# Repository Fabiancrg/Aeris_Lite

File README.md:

| Supported Targets | ESP32-C6 | ESP32-H2 |
| ----------------- |  -------- | -------- |

# Zigbee Air Quality Sensor - Aeris

This project implements a Zigbee Router that reads air quality sensors and exposes them as standard Zigbee sensor endpoints with **real-time RGB LED visual indicators**.

## Key Features

✅ **7 Zigbee Endpoints**: Temperature, Humidity, Pressure, VOC Index, NOx Index, CO2, LED Config, Status LED  
✅ **4 High-Precision Sensors**: SHT45, LPS22HB, SGP41, SCD40  
✅ **4 RGB Status LEDs**: Independent visual feedback for CO2, VOC, NOx, and Humidity  
✅ **Configurable Thresholds**: Adjust warning/danger levels via Zigbee2MQTT  
✅ **Zigbee Router**: Can accept other devices (max 10 children)  
✅ **OTA Support**: Firmware updates over Zigbee  
✅ **Factory Reset**: Boot button for easy network reset

## Hardware Requirements

- ESP32-C6 development board (or compatible)
- Air quality sensors:
  - **SHT45 Temperature and Humidity sensor** via I2C
  - **LPS22HB Pressure sensor** via I2C
  - **SGP41 VOC and NOx sensor** via I2C
  - **SCD40 CO2 sensor** via I2C
- **5× SK6812/WS2812B RGB LEDs** in daisy-chain configuration (air quality visual indicators)
  - Single GPIO20 with SN74AHCT1G125 buffer for all LEDs
  - LED chain: CO2 → VOC → NOx → Humidity → Status
- I2C connection (SDA/SCL pins configurable)
- **Power supply**: 5V USB, 500mA minimum recommended

## Features

The Zigbee air quality sensor exposes the following sensor endpoints:

### Endpoint 1: Temperature and Humidity Sensor
- **Temperature Measurement Cluster (0x0402)**: Temperature in °C
- **Relative Humidity Measurement Cluster (0x0405)**: Humidity in %
- **Sensor**: Sensirion SHT45 (I2C)
- **Temperature Range**: -40°C to +125°C
- **Temperature Accuracy**: ±0.1°C (typical, 15-40°C)
- **Humidity Range**: 0-100% RH
- **Humidity Accuracy**: ±1.0% RH (typical, 25-75% RH)
- **Measurement Time**: 8.2ms (high precision mode)
- **Conversion**: Temperature: T = -45 + 175×(S/65535), Humidity: RH = -6 + 125×(S/65535)
- **Calibration Offsets**: Custom attributes (0xF010, 0xF011) for temperature/humidity adjustment
- **Sensor Refresh Interval**: Configurable update rate (10-3600s, default 30s) via attribute 0xF012

### Endpoint 2: Pressure Sensor
- **Pressure Measurement Cluster (0x0403)**: Atmospheric pressure in hPa
- **Sensor**: STMicroelectronics LPS22HB (I2C)
- **Update Rate**: On-demand (one-shot mode for power savings)
- **Range**: 260-1260 hPa
- **Accuracy**: ±0.025 hPa (typical)
- **Measurement Time**: ~15ms per reading

### Endpoint 3: VOC Index Sensor
- **Analog Input Cluster (0x000C)**: VOC Index (1-500)
- **Sensor**: Sensirion SGP41 (I2C)
- **Description**: Volatile Organic Compounds air quality index
- **Raw signals**: VOC raw values available
- **Update Rate**: 1 Hz enforced (minimum 1-second interval per datasheet)
- **Note**: Requires temperature/humidity compensation from SHT45

### Endpoint 4: NOx Index Sensor
- **Analog Input Cluster (0x000C)**: NOx Index (1-500)
- **Sensor**: Sensirion SGP41 (I2C)
- **Description**: Nitrogen Oxides air quality index
- **Raw signals**: NOx raw values available
- **Update Rate**: 1 Hz enforced (minimum 1-second interval per datasheet)
- **Note**: Requires temperature/humidity compensation from SHT45

### Endpoint 5: CO2 Sensor
- **CO2 Concentration Cluster (0x040D)**: Carbon dioxide in ppm
- **Sensor**: Sensirion SCD40 (I2C)
- **Range**: 400-2000 ppm (optimized for indoor air quality)
- **Accuracy**: ±(40 ppm + 5% of reading)
- **Update Rate**: 5 seconds (automatic periodic measurement)
- **Pressure Compensation**: Automatic compensation using LPS22HB pressure data
- **Calibration**: Automatic self-calibration (ASC) disabled for stable baseline in controlled environments
- **Additional**: Built-in temperature and humidity sensor (bonus)

### Endpoint 6: LED Configuration
- **On/Off Cluster (0x0006)**: Master switch to enable/disable all RGB status LEDs
- **Custom Attributes (0xF000-0xF00C)**: Configurable air quality thresholds and individual LED control
- **Bitmask Control (0xF00C)**: Individual enable/disable for each of the 4 LEDs
- **Thresholds**: Adjustable orange/red warning levels for VOC, NOx, CO2, Humidity

### Endpoint 7: Status LED
- **On/Off Cluster (0x0006)**: Enable/disable Zigbee status LED
- **Automatic Status Indication**: Shows Zigbee network connection status
  - 🟢 **Green**: Successfully connected to coordinator
  - 🟡 **Blinking Green/Orange**: Joining network
  - 🟠 **Orange**: Not joined to network
  - 🔴 **Red**: Error during initialization
- **GPIO**: GPIO8 (built-in LED on ESP32-C6 Supermini)

### RGB LED Air Quality Indicators

The device includes **4 separate RGB LEDs (SK6812)** that provide real-time visual feedback for air quality:

### LED Indicators
- **CO2 LED** (GPIO1): Shows carbon dioxide level status
- **VOC LED** (GPIO18): Shows volatile organic compounds status
- **NOx LED** (GPIO15): Shows nitrogen oxides status
- **Humidity LED** (GPIO14): Shows humidity level status

### Color Coding
Each LED independently displays:
- 🟢 **Green**: Parameter is in good/healthy range
- 🟠 **Orange**: Parameter is not ideal (warning level)
- 🔴 **Red**: Parameter is poor/unhealthy (danger level)

### Features
- **Independent operation**: Each LED shows only its corresponding sensor
- **At-a-glance status**: Quickly identify which parameter needs attention
- **Configurable thresholds**: Adjust warning/danger levels via Zigbee2MQTT
- **Brightness control**: Adjustable LED brightness (1-255) via Level Control cluster
- **Settings persistence**: All LED settings, thresholds, and calibrations stored in NVS (survive reboots)
- **Dual control**:
  - **Master switch**: Enable/disable all sensor LEDs at once (On/Off cluster)
  - **Individual control**: Enable/disable each LED separately via bitmask (0xF00C)
  - **Status LED control**: Independent on/off control for Zigbee status LED (endpoint 10)
- **Low power**: LEDs only update when color changes

### LED Control

**Master On/Off Switch:**
- Turn all LEDs on/off regardless of individual settings
- Located in On/Off cluster (standard Zigbee)

**Individual LED Bitmask (0xF00C):**
- Control each LED independently using a single 8-bit value
- Each bit represents one LED (1=enabled, 0=disabled)
- Bit assignments:
  - Bit 0 (0x01): CO2 LED
  - Bit 1 (0x02): VOC LED
  - Bit 2 (0x04): NOx LED
  - Bit 4 (0x10): Humidity LED
- Default: `0x17` (all LEDs enabled)

**Examples:**
```
0x17 (23)  - All LEDs enabled
0x03 (3)   - Only CO2 and VOC enabled
0x04 (4)   - Only NOx enabled
0x05 (5)   - CO2 and NOx enabled
0x00 (0)   - All LEDs disabled (individual level)
```

### Default Thresholds (all configurable)
- **VOC Index**: Orange ≥150, Red ≥250
- **NOx Index**: Orange ≥150, Red ≥250
- **CO2**: Orange ≥1000 ppm, Red ≥1500 ppm
- **Humidity**: Orange <30% or >70%, Red <20% or >80%

See [LED Configuration Guide](LED_CONFIGURATION.md) for detailed setup and usage.

## I2C and UART Configuration

### I2C Bus (Temperature, Humidity, Pressure, VOC, CO2)

The device communicates with most sensors via I2C:

- **SDA Pin**: GPIO 6 (configurable in `aeris_driver.h`)
- **SCL Pin**: GPIO 7 (configurable in `aeris_driver.h`)
- **Frequency**: 100 kHz
- **Pull-ups**: Internal pull-ups enabled

**I2C Addresses:**
- SHT45 (Temp/Humidity): 0x44 (fixed address)
- LPS22HB (Pressure): 0x5C (default, SA0=0) or 0x5D (SA0=1)
- SGP41 (VOC/NOx): 0x59 (fixed address)
- SCD40 (CO2): 0x62 (fixed address)

## Project Structure

```
Aeris_zb/
├── main/
│   ├── esp_zb_aeris.c         # Main Zigbee application
│   ├── esp_zb_aeris.h         # Zigbee configuration header
│   ├── aeris_driver.c         # Air quality sensor driver implementation
│   ├── aeris_driver.h         # Sensor driver header
│   ├── led_indicator.c        # RGB LED driver (6 LEDs via RMT)
│   ├── led_indicator.h        # LED driver header
│   ├── settings.c             # NVS settings persistence
│   ├── settings.h             # Settings header
│   ├── esp_zb_ota.c           # OTA update support
│   ├── esp_zb_ota.h           # OTA header
│   ├── board.h                # Board pin definitions (GPIO mapping)
│   ├── CMakeLists.txt         # Component build configuration
│   └── idf_component.yml      # Component dependencies
├── CMakeLists.txt             # Project CMakeLists
├── sdkconfig                  # ESP-IDF configuration
├── README.md                  # This file
├── LED_CONFIGURATION.md   # LED setup and Zigbee2MQTT integration
├── LED_IMPLEMENTATION.md  # LED technical implementation details
└── ENDPOINT_MAP.md        # Complete Zigbee endpoi
```

## Building and Flashing

1. Set up ESP-IDF v5.5.1 or later
2. Configure the project:
   ```bash
   idf.py set-target esp32c6
   idf.py menuconfig
   ```
3. Build the project:
   ```bash
   idf.py build
   ```
4. Flash to device:
   ```bash
   idf.py -p COMx flash monitor
   ```

## Configuration

### Zigbee Configuration

The device is configured as a Zigbee Router:
- **Endpoints**: 1-7 (sensor data + LED configuration + status LED)
  - Endpoints 1-5: Sensor data (Temperature, Humidity, Pressure, VOC, NOx, CO2)
  - Endpoint 6: Air quality LED configuration and control
  - Endpoint 7: Zigbee status LED control
- **Profile**: Home Automation (0x0104)
- **Device IDs**: Various sensor types + On/Off output for LED control
- **Channel Mask**: All channels
- **Max Children**: 10 (router can accept other devices)

### LED Configuration

**Air Quality LEDs (4 LEDs)** - Configure via Zigbee2MQTT endpoint 6:
- **Master On/Off**: Single switch to enable/disable all LEDs (On/Off cluster)
- **Individual Control**: Bitmask attribute (0xF00C) for per-LED enable/disable
  - Set to `0x17` (23) for all LEDs
  - Set to `0x03` (3) for CO2 + VOC only
  - Set to `0x00` (0) to disable all (at individual level)
- **Thresholds**: 8 configurable attributes (VOC, NOx, CO2, Humidity orange/red levels)
- **GPIO Pins**: Configurable in `main/board.h` (defaults: GPIO1, 18, 15, 14)

**Control Logic:**
- Master OFF → All LEDs off (ignores bitmask)
- Master ON + bit set → LED shows sensor status color
- Master ON + bit clear → LED off

**Zigbee Status LED (1 LED)** - Configure via Zigbee2MQTT endpoint 7:
- **On/Off Control**: Enable/disable status LED
- **Automatic Status Indication**:
  - 🟢 **Green**: Successfully connected to Zigbee coordinator
  - 🟡 **Blinking Green/Orange**: Actively joining network (searching for coordinator)
  -  **Orange**: Not joined to any network or left the network (idle)
  - 🔴 **Red**: Error during initialization or join failed
- **GPIO Pin**: GPIO23 (configurable in `main/board.h`)
- **Blink Pattern**: 500ms interval during network join process

See [LED Configuration Guide](LED_CONFIGURATION.md) for detailed threshold settings.

### Sensor Configuration

Configure sensor I2C addresses and settings in `aeris_driver.c`:
- Default I2C pins: SDA=GPIO6, SCL=GPIO7
- Adjust pins in `aeris_driver.h` if needed

### Joining the Network

On first boot, the device will automatically enter network steering mode. Once joined, the device will save the network credentials and automatically rejoin on subsequent boots.

## Usage

### From Zigbee Coordinator (e.g., Zigbee2MQTT, Home Assistant)

1. Put your coordinator in pairing mode
2. Power on the ESP32-C6 device
3. Wait for the device to join (check logs - status LED will turn green when connected)
4. The air quality sensor will appear with the following entities:
   - Temperature (°C)
   - Humidity (%)
   - Pressure (hPa)
   - VOC Index (1-500)
   - NOx Index (1-500)
   - CO2 (ppm)
   - **Air Quality LED Master Switch** (On/Off - controls all 4 air quality LEDs)
   - **LED Enable Mask** (0-15 - individual LED control)
   - **LED Thresholds** (configurable warning/danger levels)
   - **Status LED Switch** (On/Off - controls Zigbee status LED)

### LED Control Examples

**Via Zigbee2MQTT:**

```javascript
// Turn all sensor LEDs on (master switch)
await publish('zigbee2mqtt/aeris/set', {state: 'ON'});

// Turn all sensor LEDs off (master switch)
await publish('zigbee2mqtt/aeris/set', {state: 'OFF'});

// Set LED brightness (1-255, default 128)
await publish('zigbee2mqtt/aeris/set', {brightness: 128});
await publish('zigbee2mqtt/aeris/set', {brightness: 255});  // Max brightness
await publish('zigbee2mqtt/aeris/set', {brightness: 64});   // Dim

// Enable all 4 LEDs individually (bitmask)
await publish('zigbee2mqtt/aeris/set', {led_enable_mask: 15});  // 0x0F

// Enable only CO2 and VOC LEDs
await publish('zigbee2mqtt/aeris/set', {led_enable_mask: 3});   // 0x03

// Enable only NOx LED
await publish('zigbee2mqtt/aeris/set', {led_enable_mask: 4});   // 0x04

// Enable CO2, VOC, and Humidity LEDs
await publish('zigbee2mqtt/aeris/set', {led_enable_mask: 11});  // 0x0B

// Disable all LEDs via bitmask (master can still be ON)
await publish('zigbee2mqtt/aeris/set', {led_enable_mask: 0});

// Status LED control (endpoint 10)
await publish('zigbee2mqtt/aeris_status/set', {state: 'ON'});   // Enable status LED
await publish('zigbee2mqtt/aeris_status/set', {state: 'OFF'});  // Disable status LED

// Calibration offsets (stored in NVS)
await publish('zigbee2mqtt/aeris/set', {temperature_offset: 5});   // +0.5°C
await publish('zigbee2mqtt/aeris/set', {temperature_offset: -10}); // -1.0°C
await publish('zigbee2mqtt/aeris/set', {humidity_offset: 20});     // +2.0% RH

// Sensor refresh interval (10-3600 seconds, default 30)
await publish('zigbee2mqtt/aeris/set', {sensor_refresh_interval: 60}); // 1 minute
```

### Visual LED Status

**Air Quality LEDs (4 RGB LEDs)** provide real-time visual feedback:
- **CO2 LED**: Green/Orange/Red based on CO2 levels
- **VOC LED**: Green/Orange/Red based on VOC Index
- **NOx LED**: Green/Orange/Red based on NOx Index
- **Humidity LED**: Green/Orange/Red based on humidity range

**Status LED (1 RGB LED)** shows Zigbee network state:
- 🟢 **Green**: Connected to coordinator
- 🟡 **Blinking Green/Orange**: Joining network (searching)
- 🟠 **Orange**: Not joined or left network (idle)
- 🔴 **Red**: Join failed or error state (will retry)

**At a glance**, you can see:
- All green (air quality) = Excellent air quality
- Mixed colors = Some parameters need attention
- Status LED solid green = Device is online and connected
- Status LED blinking = Device is trying to join network
- Red LEDs = Immediate action needed (ventilate, increase/decrease humidity, etc.)

Configure thresholds in Zigbee2MQTT to match your preferences. See [LED Configuration Guide](LED_CONFIGURATION.md).

### Sensor Reading Updates

- Sensors are polled periodically (configurable interval)
- Values are reported to the Zigbee coordinator when they change
- All endpoints support binding and reporting configuration

## Supported Sensors

This project provides a framework for air quality sensors. You'll need to implement the actual sensor drivers:

### Temperature/Humidity
- **SHT45** (implemented): Sensirion high-precision sensor
  - I2C interface (address 0x44)
  - Temperature: -40 to +125°C, ±0.1°C accuracy
  - Humidity: 0-100% RH, ±1.0% RH accuracy
  - High repeatability mode: 8.2ms measurement time
  - CRC-8 checksum for data integrity
  - Serial number readout
  - Soft reset command
  - Low power: 0.4 µA idle
- **Alternative**: SHT4x series, BME280, DHT22

### Pressure
- **LPS22HB** (implemented): STMicroelectronics MEMS pressure sensor
  - I2C interface (address 0x5C or 0x5D)
  - Measures 260-1260 hPa
  - ±0.025 hPa accuracy
  - Internal temperature sensor (bonus)
  - Low power: 3 µA @ 1Hz
  - Configurable output rate (1-75 Hz)
- **Alternative**: BMP280, BME280 (Bosch sensors)

### VOC and NOx Index
- **SGP41** (implemented): Sensirion VOC and NOx sensor
  - I2C interface (address 0x59)
  - Dual gas sensing: VOC + NOx
  - Separate Zigbee endpoints for VOC (endpoint 6) and NOx (endpoint 7)
  - Raw signal output (requires algorithm)
  - Temperature/humidity compensation
  - Built-in heater for measurement
  - Low power: 2.6 mA average @ 1Hz
  - Serial number readout
  - Self-test capability
- **Note**: Full Gas Index Algorithm integration recommended for production
- **Alternative**: SGP40 (VOC only), BME680 (combo sensor)

### CO2
- **SCD40** (implemented): Sensirion NDIR CO2 sensor
  - I2C interface (address 0x62)
  - Range: 400-2000 ppm (indoor air quality)
  - Accuracy: ±(40 ppm + 5%)
  - Automatic periodic measurement every 5 seconds
  - **Ambient pressure compensation** from LPS22HB sensor
  - Built-in temperature and humidity sensor
  - Automatic self-calibration (ASC)
  - CRC-8 data validation
  - Serial number readout
  - Low power: 15 mA average @ 1 measurement/5s
- **Alternative**: SCD41 (extended range 400-5000 ppm)

## Implementation Notes

The `aeris_driver.c` file contains:

1. **SHT45 implementation** (complete):
   - I2C initialization and device detection
   - Soft reset on startup
   - Serial number readout and verification
   - High repeatability measurement mode
   - CRC-8 validation on all data
   - Temperature and humidity conversion
   - Humidity clamping to 0-100% range

2. **LPS22HB implementation** (complete):
   - I2C initialization and device detection
   - WHO_AM_I verification (0xB1)
   - 25 Hz output data rate
   - Block data update enabled
   - Pressure reading in hPa
   - Temperature reading included

4. **SGP41 implementation** (complete):
   - I2C initialization and device detection
   - Serial number readout and verification
   - Self-test execution
   - Raw VOC and NOx signal measurement
   - Separate VOC and NOx index reporting (endpoints 6 and 7)
   - Temperature/humidity compensation support
   - CRC8 validation on all data
   - Placeholder index calculation (needs Gas Index Algorithm)

5. **SCD40 implementation** (complete):
   - I2C initialization and device detection
   - Serial number readout and verification
   - Automatic periodic measurement mode
   - CO2, temperature, and humidity reading
   - Ambient pressure compensation using LPS22HB data
   - CRC-8 validation on all data
   - Data ready status checking
   - 5-second measurement interval

## Sensor Wiring Diagrams

### SHT45 Wiring

```
SHT45 Pin → ESP32-C6
VDD       → 3.3V
GND       → GND
SCL       → GPIO 7
SDA       → GPIO 6
```

**Note**: SHT45 operates at 3.3V. No level shifters needed with ESP32-C6.

### LPS22HB Wiring

```
LPS22HB Pin → ESP32-C6
VDD         → 3.3V
GND         → GND
SCL         → GPIO 7 (I2C SCL)
SDA         → GPIO 6 (I2C SDA)
SA0         → GND (for address 0x5C) or 3.3V (for 0x5D)
```

**Note**: LPS22HB operates at 1.7-3.6V. Use 3.3V supply.

### SGP41 Wiring

```
SGP41 Pin → ESP32-C6
VDD       → 3.3V
GND       → GND
SCL       → GPIO 7 (I2C SCL)
SDA       → GPIO 6 (I2C SDA)
```

**Note**: SGP41 operates at 1.7-3.6V. Use 3.3V supply. No external pull-ups needed on most breakout boards.

### SCD40 Wiring

```
SCD40 Pin → ESP32-C6
VDD       → 3.3V
GND       → GND
SCL       → GPIO 7 (I2C SCL)
SDA       → GPIO 6 (I2C SDA)
```

**Note**: SCD40 operates at 2.4-5.5V. Use 3.3V supply. Automatic periodic measurement every 5 seconds. Benefits from ambient pressure compensation provided by LPS22HB sensor.

### SK6812 RGB LED Wiring (5 LEDs)

The device uses 5 separate RGB LEDs for visual air quality feedback:

```
LED Purpose    GPIO    Connection
━━━━━━━━━━━━━━━━━━━━━━━━━━━━━━━━━━━━━━━
CO2 LED        1       Data line
VOC LED        18      Data line
NOx LED        15      Data line
Humidity LED   14      Data line
Status LED     8       Data line (Zigbee status)

For each LED:
  Data → GPIO pin (see table above)
  VCC  → 5V (SK6812 specification)
  GND  → GND
```

**Notes**: 
- SK6812 LEDs use WS2812 protocol via RMT peripheral
- Each LED operates independently showing its sensor's status
- All 5 sensor LEDs can be enabled/disabled together via Zigbee (endpoint 9)
- Status LED controlled separately via endpoint 10
- Brightness adjustable 1-255 via Level Control cluster
- GPIO pins are configurable in `main/board.h`
- Total LED current (all 6 at max brightness): ~360mA

**Color Codes**:
- 🟢 Green = Good air quality for that parameter
- 🟠 Orange = Warning level (not ideal)
- 🔴 Red = Danger level (poor air quality)

See [LED Configuration Guide](LED_CONFIGURATION.md) for threshold configuration via Zigbee2MQTT.

### Important: Gas Index Algorithm

The SGP41 currently uses a **simplified placeholder** for VOC/NOx index calculation. For production use, integrate Sensirion's **Gas Index Algorithm**:

- Download from: https://github.com/Sensirion/gas-index-algorithm
- Provides proper VOC Index (1-500) and NOx Index (1-500)
- Requires learning period (~10 minutes for VOC, ~12 hours for NOx)
- Handles baseline tracking and auto-calibration

## Troubleshooting

### Sensors not responding
- **I2C sensors**:
  - Verify I2C wiring (SDA/SCL connections)
  - Check I2C pull-up resistors (usually 4.7kΩ)
  - Verify sensor power supply (3.3V for SHT45, LPS22HB, SGP41, SCD40)
  - Use `i2cdetect` to scan for sensor addresses
  - Monitor I2C traffic in logs
  - **SHT45**: Read serial number to verify communication
  - **SHT45**: Check CRC errors in logs
  - **LPS22HB**: Check WHO_AM_I register (should be 0xB1)
  - **LPS22HB**: Verify address 0x5C or 0x5D (depends on SA0 pin)
  - **SGP41**: Check serial number readout
  - **SGP41**: Verify self-test passes (result 0xD400)
  - **SGP41**: Ensure temperature/humidity data is available for compensation
  - **SCD40**: Check serial number readout
  - **SCD40**: Verify data ready status (measurements every 5 seconds)
  - **SCD40**: Check CRC errors in logs

**Power Note**: 
- **5 LEDs** (4 air quality + 1 status) at full brightness: ~300mA
- **ESP32-C6 + sensors**: ~50-80mA
- **Total**: ~350-380mA
- **Recommended power supply**: 500mA minimum (USB 5V)

### Build errors
- Make sure ESP-IDF v5.5.1+ is installed
- Run `idf.py fullclean` and rebuild
- Check that all sensor libraries are in `idf_component.yml`

---

## 🙌 Credits

- Zigbee2MQTT ecosystem: [Koenkk/zigbee2mqtt](https://github.com/Koenkk/zigbee2mqtt) and [zigbee-herdsman-converters](https://github.com/Koenkk/zigbee-herdsman-converters)
- Base Zigbee framework: Espressif ESP-IDF examples

## 🛡️ License

This repository uses multiple licenses depending on content type:

- **Code** (`*.c`, `*.h`, `*.yaml`) — [GNU GPLv3](./LICENSE)  
- **PCB files** (`*.zip`, `*.json`) — [CC BY-NC-SA 4.0](./LICENSE-hardware)

---

## ⚠️ Disclaimer

This project is provided as-is, without any warranty or guarantee of fitness for a particular purpose. Use at your own risk. The authors and contributors are not responsible for any damage, malfunction, or loss resulting from the use, modification, or installation of this hardware or software.

- This is an open-source, community-driven project intended for educational and experimental use.
- The hardware and firmware are not certified for commercial or safety-critical applications.
- Always follow proper electrical safety procedures when working with sensors and embedded systems.
- Modifying or installing this project may void your equipment warranty.
- Ensure compliance with local laws and regulations regarding wireless devices.

By using this project, you acknowledge and accept these terms.

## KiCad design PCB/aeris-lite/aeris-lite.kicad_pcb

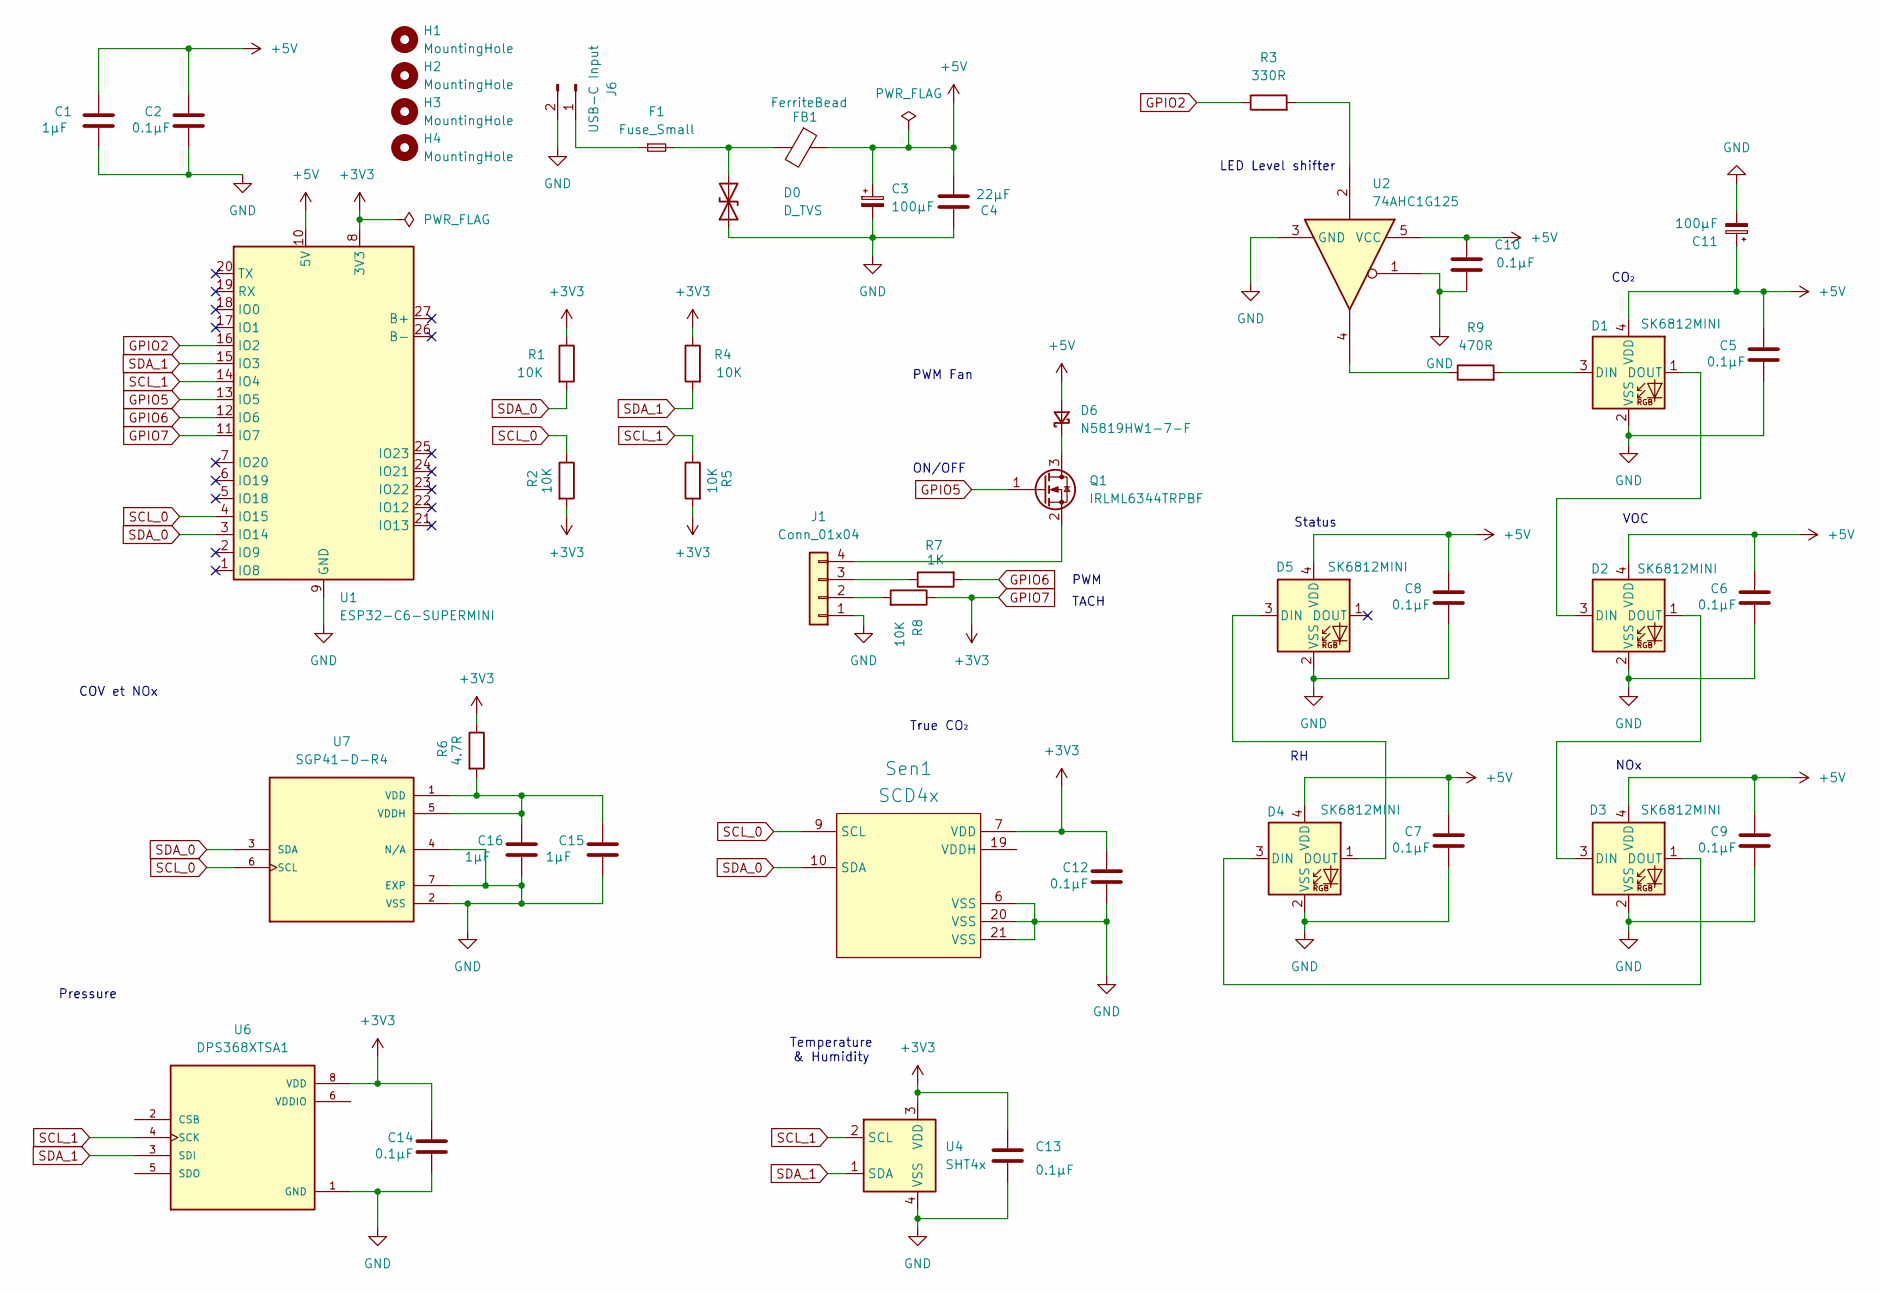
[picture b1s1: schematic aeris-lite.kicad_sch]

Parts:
C1, C15, C16: 1µF; C_0805_2012Metric
C2, C5, C6, C7, C8, C9, C10, C12, C13, C14: 0.1µF; C_0805_2012Metric
C3, C11: 100µF; CP_Elec_6.3x5.9
C4: 22µF; C_0805_2012Metric
D0: D_TVS; D_SMB
D1, D2, D3, D4, D5: SK6812MINI; LED_SK6812MINI_PLCC4_3.5x3.5mm_P1.75mm
D6: N5819HW1-7-F; D_SOD-123F
F1: Fuse_Small; Fuse_1206_3216Metric
FB1: FerriteBead; L_1206_3216Metric
H1, H2, H3, H4: MountingHole; MountingHole_2.2mm_M2
J1: Conn_01x04; JST_GH_SM04B-GHS-TB_1x04-1MP_P1.25mm_Horizontal
J6: USB-C Input; PinHeader_1x02_P2.54mm_Vertical
Q1: IRLML6344TRPBF; SOT-23
R1, R2, R4, R5, R8: 10K; R_0805_2012Metric
R3: 330R; R_0805_2012Metric
R6: 4.7R; R_0805_2012Metric
R7: 1K; R_0805_2012Metric
R9: 470R; R_0805_2012Metric
Sen1: SCD4x; Sensirion_SCD4x-1EP_10.1x10.1mm_P1.25mm_EP4.8x4.8mm
U1: ESP32-C6-SUPERMINI; ESP32C6-Supermini
U2: 74AHC1G125; SOT-23-5
U4: SHT4x; Sensirion_DFN-4_1.5x1.5mm_P0.8mm_SHT4x_NoCentralPad
U6: DPS368XTSA1; XDCR_DPS368XTSA1
U7: SGP41-D-R4; XDCR_SGP41-D-R4; PARTREV 1.0

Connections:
+5V: C1.1, C2.1, C3.1, C4.2, C5.1, C6.1, C7.1, C8.1, C9.1, C10.1, C11.1, D1.4 (VDD), D2.4 (VDD), D3.4 (VDD), D4.4 (VDD), D5.4 (VDD), D6.2 (A), FB1.1, U1.10 (5V), U2.5 (VCC)
GND: C1.2, C2.2, C3.2, C4.1, C5.2, C6.2, C7.2, C8.2, C9.2, C10.2, C11.2, C12.2, C13.2, C14.2, C15.2, C16.2, D0.1 (A1), D1.2 (VSS), D2.2 (VSS), D3.2 (VSS), D4.2 (VSS), D5.2 (VSS), J1.1, J6.2, Sen1.6 (VSS), Sen1.20 (VSS), Sen1.21 (VSS), U1.9 (GND), U2.1, U2.3 (GND), U4.4 (VSS), U6.1 (GND), U6.7 (GND), U7.2 (VSS), U7.4 (N/A), U7.7 (EXP)
GPIO2: R3.1, U1.16 (IO2)
GPIO5: Q1.1 (G), U1.13 (IO5)
GPIO6: R7.2, U1.12 (IO6)
GPIO7: C12.1, C13.1, C14.1, R1.1, R2.2, R4.1, R5.2, R6.1, R8.1, Sen1.7 (VDD), U1.8 (3V3), U1.11 (IO7), U4.3 (VDD), U6.8 (VDD)
unnamed: D0.2 (A2), F1.2, FB1.2
unnamed: D1.3 (DIN), R9.2
unnamed: D1.1 (DOUT), D2.3 (DIN)
unnamed: D2.1 (DOUT), D3.3 (DIN)
unnamed: D3.1 (DOUT), D4.3 (DIN)
unnamed: D4.1 (DOUT), D5.3 (DIN)
unnamed: D6.1 (K), Q1.3 (D)
unnamed: J1.2, R8.2
unnamed: J1.3, R7.1
unnamed: J1.4, Q1.2 (S)
unnamed: F1.1, J6.1
unnamed: R3.2, U2.2
unnamed: R9.1, U2.4
unnamed: C15.1, C16.1, R6.2, U7.1 (VDD), U7.5 (VDDH)
SCL_0: R2.1, Sen1.9 (SCL), U1.4 (IO15), U7.6 (SCL)
SCL_1: R5.1, U1.14 (IO4), U4.2 (SCL), U6.4 (SCK)
SDA_0: R1.2, Sen1.10 (SDA), U1.3 (IO14), U7.3 (SDA)
SDA_1: R4.2, U1.15 (IO3), U4.1 (SDA), U6.3 (SDI)

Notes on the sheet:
TACH
VOC
Pressure
ON/OFF
True CO₂
Temperature & Humidity
LED Level shifter
CO₂
Status
PWM
PWM Fan
NOx
COV et NOx

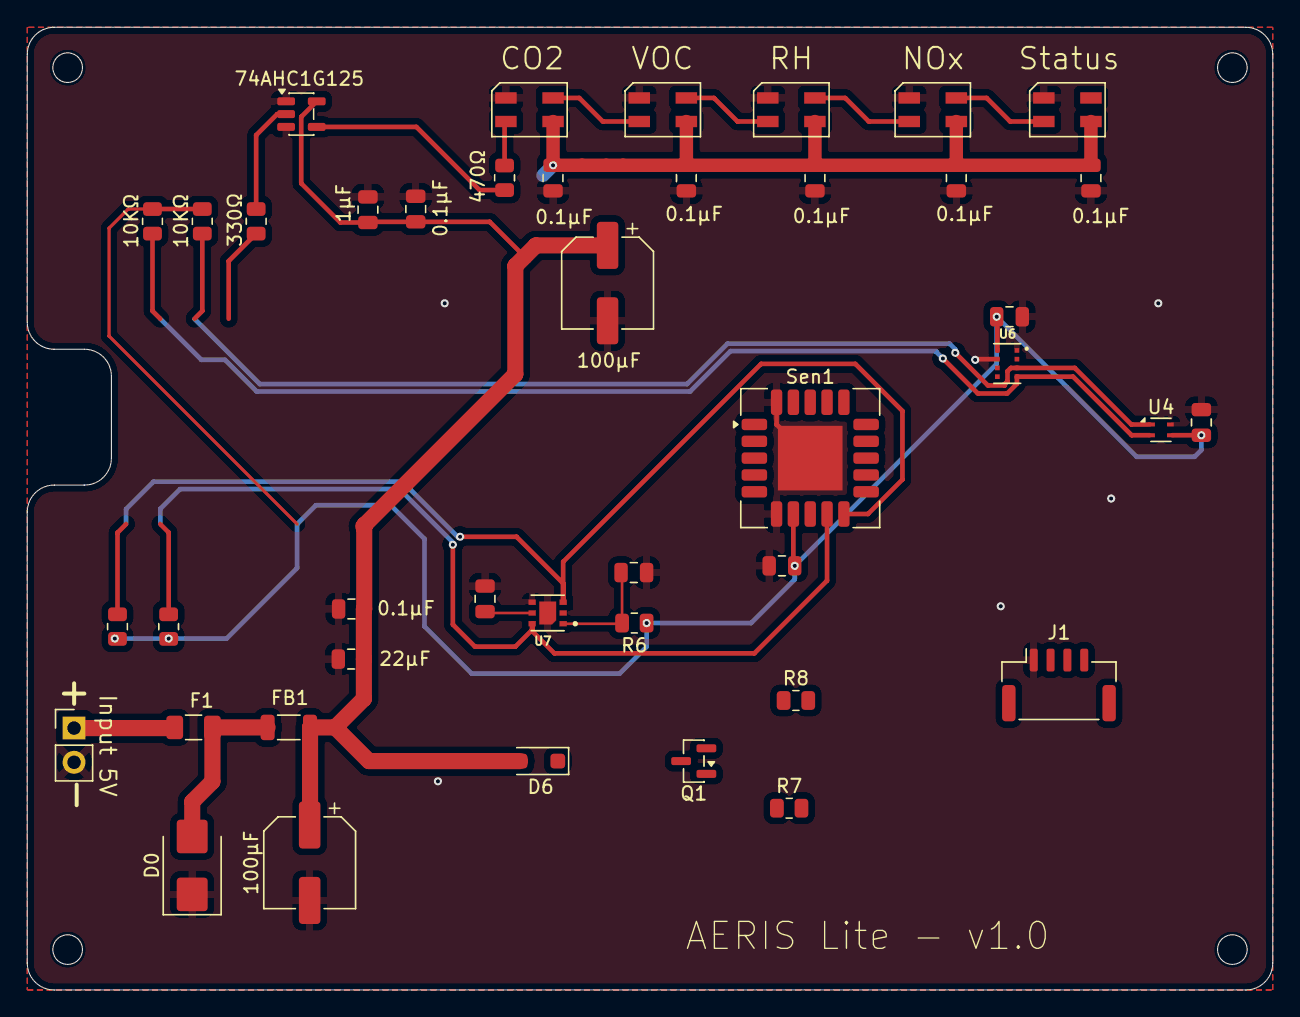
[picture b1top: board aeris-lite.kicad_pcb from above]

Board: 2 copper layers, 92.5 x 71.5 mm, 46 parts (0 on the bottom side), 21 nets.

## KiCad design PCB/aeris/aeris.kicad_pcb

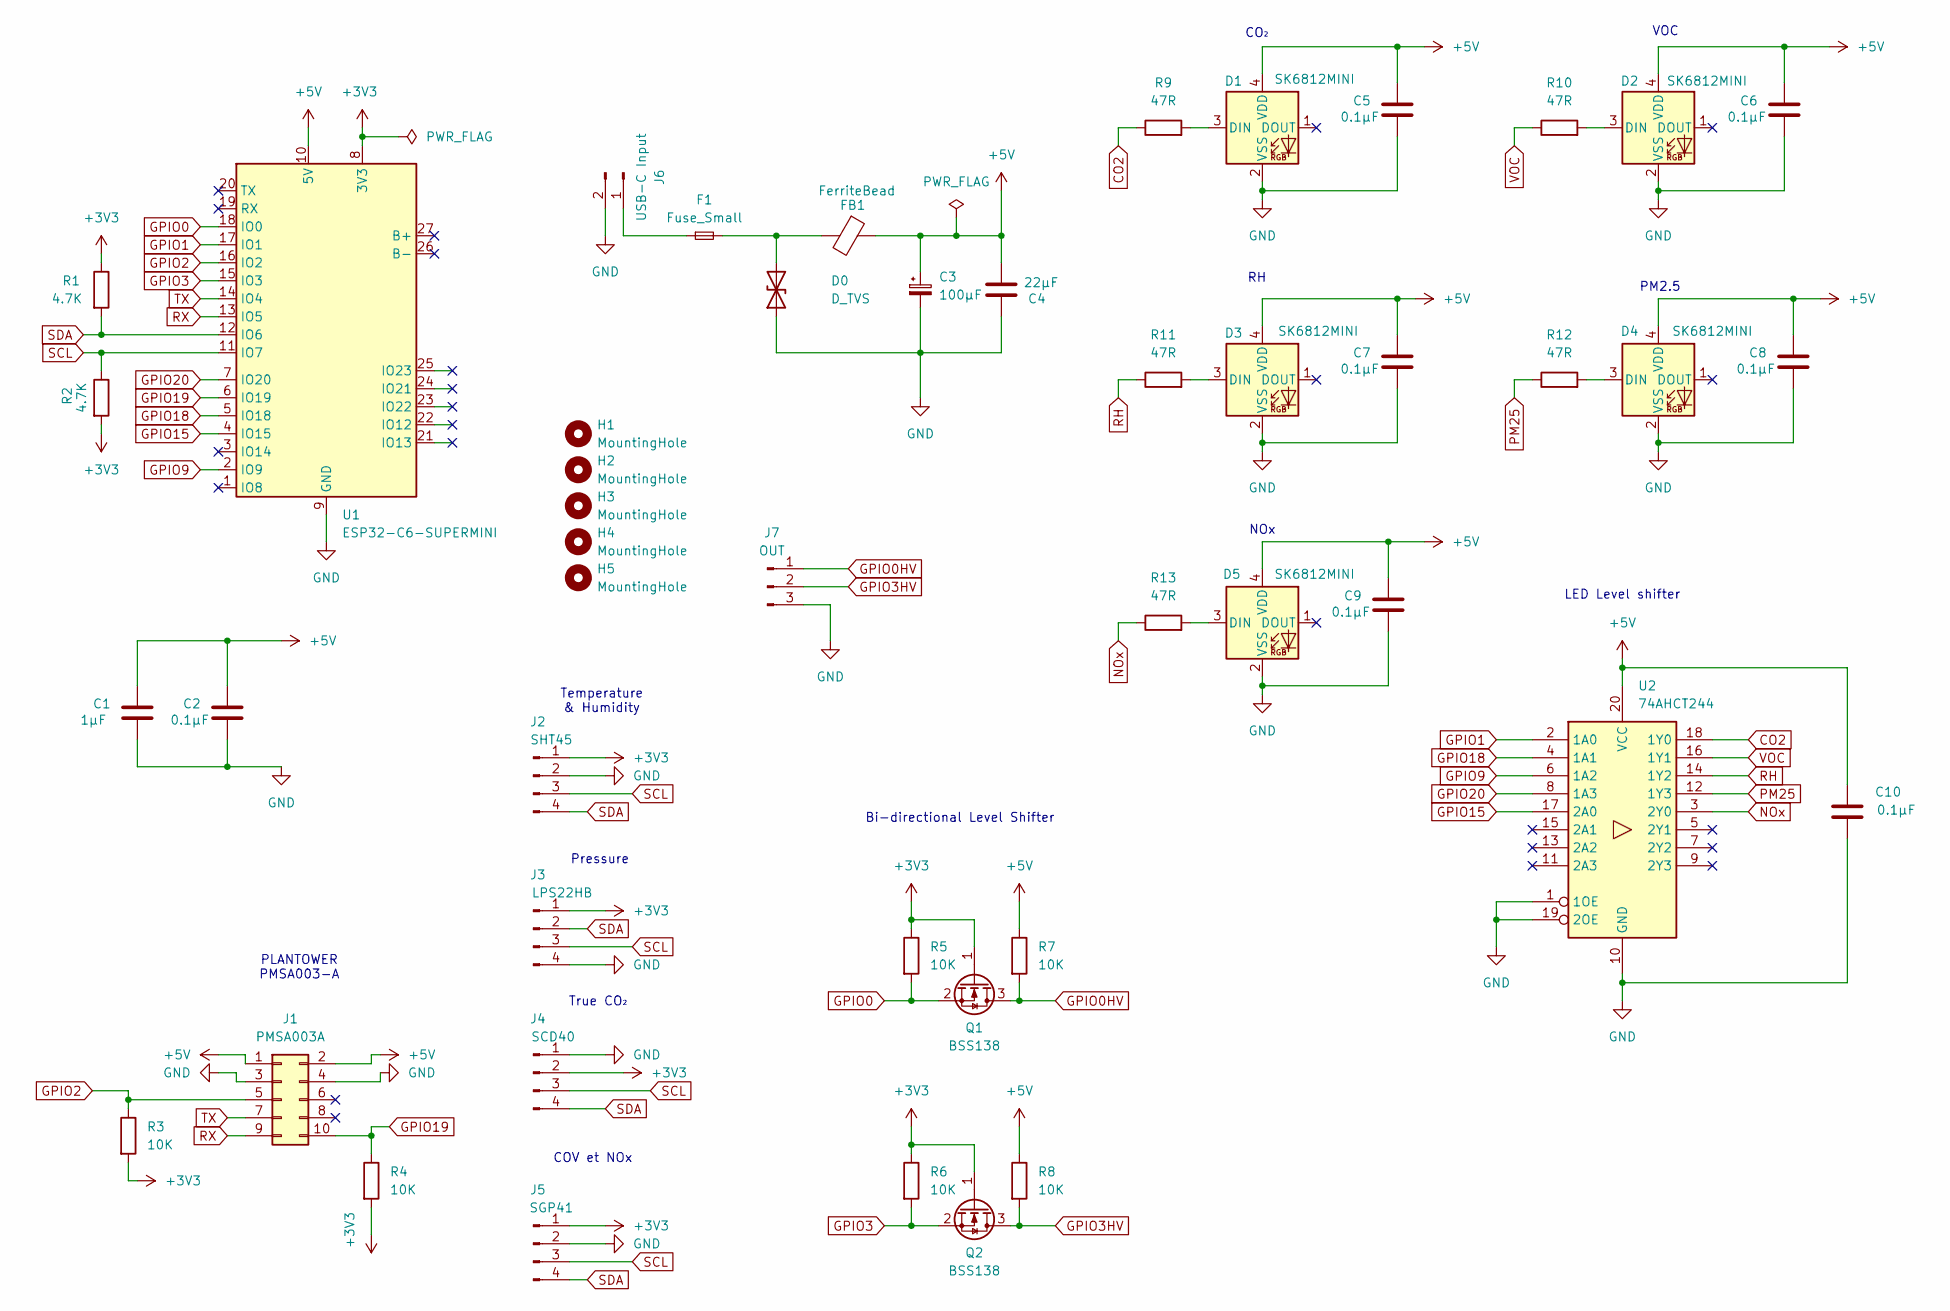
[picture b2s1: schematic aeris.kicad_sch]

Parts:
C1: 1µF; C_1206_3216Metric
C2, C5, C6, C7, C8, C9, C10: 0.1µF; C_0805_2012Metric
C3: 100µF; CP_Elec_6.3x5.9
C4: 22µF; C_0805_2012Metric
D0: D_TVS; D_SMB
D1, D2, D3, D4, D5: SK6812MINI; LED_SK6812MINI_PLCC4_3.5x3.5mm_P1.75mm
F1: Fuse_Small; Fuse_1206_3216Metric
FB1: FerriteBead; L_1206_3216Metric
H1, H2, H3, H4, H5: MountingHole; MountingHole_2.2mm_M2
J1: PMSA003A; PLANTOWER_PMSA003-A
J2: SHT45; SHT45-Breakout
J3: LPS22HB; LPS22HB-Breakout
J4: SCD40; SCD40-Breakout
J5: SGP41; SGP41-Breakout
J6: USB-C Input; PinHeader_1x02_P2.54mm_Vertical
J7: OUT; PinHeader_1x03_P2.54mm_Vertical
Q1, Q2: BSS138; SOT-23
R1, R2: 4.7K; R_0805_2012Metric
R3, R4, R5, R6, R7, R8: 10K; R_0805_2012Metric
R9, R10, R11, R12, R13: 47R; R_0805_2012Metric
U1: ESP32-C6-SUPERMINI; ESP32C6-Supermini
U2: 74AHCT244; SOIC-20W_7.5x12.8mm_P1.27mm

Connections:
+3V3: J2.1, J3.1, J4.2, J5.1, Q1.1 (G), Q2.1 (G), R1.1, R2.2, R3.2, R4.2, R5.1, R6.1, U1.8 (3V3)
+5V: C1.1, C2.1, C3.1, C4.2, C5.1, C6.1, C7.1, C8.1, C9.1, C10.1, D1.4 (VDD), D2.4 (VDD), D3.4 (VDD), D4.4 (VDD), D5.4 (VDD), FB1.1, J1.1, J1.2, R7.1, R8.1, U1.10 (5V), U2.20 (VCC)
CO2: R9.1, U2.18 (1Y0)
GND: C1.2, C2.2, C3.2, C4.1, C5.2, C6.2, C7.2, C8.2, C9.2, C10.2, D0.1 (A1), D1.2 (VSS), D2.2 (VSS), D3.2 (VSS), D4.2 (VSS), D5.2 (VSS), J1.3, J1.4, J2.2, J3.4, J4.1, J5.2, J6.2, J7.3, U1.9 (GND), U2.1 (1OE), U2.10 (GND), U2.19 (2OE)
GPIO0: Q1.2 (S), R5.2, U1.18 (IO0)
GPIO0HV: J7.1, Q1.3 (D), R7.2
GPIO1: U1.17 (IO1), U2.2 (1A0)
GPIO2: J1.5, R3.1, U1.16 (IO2)
GPIO3: Q2.2 (S), R6.2, U1.15 (IO3)
GPIO3HV: J7.2, Q2.3 (D), R8.2
GPIO14: U1.2 (IO9), U1.3 (IO14), U2.6 (1A2)
GPIO15: U1.4 (IO15), U2.17 (2A0)
GPIO18: U1.5 (IO18), U2.4 (1A1)
GPIO19: J1.10, R4.1, U1.6 (IO19)
GPIO20: U1.7 (IO20), U2.8 (1A3)
NOx: R13.1, U2.3 (2Y0)
unnamed: D0.2 (A2), F1.2, FB1.2
unnamed: D1.3 (DIN), R9.2
unnamed: D2.3 (DIN), R10.2
unnamed: D3.3 (DIN), R11.2
unnamed: D4.3 (DIN), R12.2
unnamed: D5.3 (DIN), R13.2
unnamed: F1.1, J6.1
PM25: R12.1, U2.12 (1Y3)
RH: R11.1, U2.14 (1Y2)
RX: J1.9, U1.13 (IO5)
SCL: J2.3, J3.3, J4.3, J5.3, R2.1, U1.11 (IO7)
SDA: J2.4, J3.2, J4.4, J5.4, R1.2, U1.12 (IO6)
TX: J1.7, U1.14 (IO4)
VOC: R10.1, U2.16 (1Y1)

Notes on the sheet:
VOC
Pressure
True CO₂
Temperature & Humidity
LED Level shifter
CO₂
PM2.5
PLANTOWER PMSA003-A
Bi-directional Level Shifter
NOx
COV et NOx

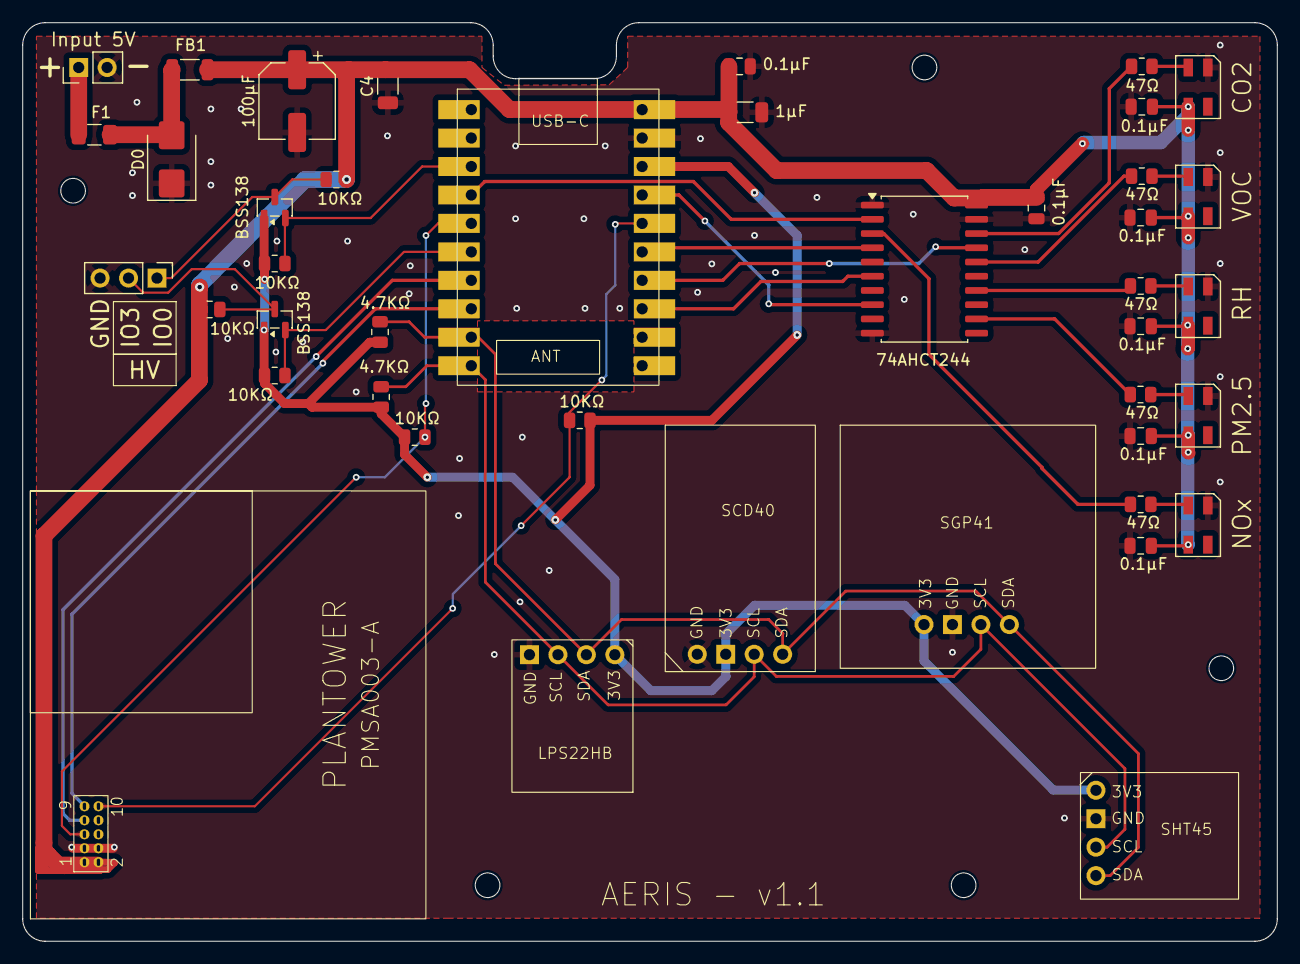
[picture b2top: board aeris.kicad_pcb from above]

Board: 2 copper layers, 112.0 x 82.0 mm, 47 parts (0 on the bottom side), 30 nets.

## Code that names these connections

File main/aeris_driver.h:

/*
 * Aeris Air Quality Sensor Driver Header
 *
 * Handles I2C/UART communication with air quality sensors
 * Supports Temperature, Humidity, Pressure, PM, VOC Index, and CO2 sensors
 */

#pragma once

#include <stdint.h>
#include <stdbool.h>
#include "esp_err.h"
#include "driver/i2c_master.h"

#ifdef __cplusplus
extern "C" {
#endif

/* Air Quality Sensor State structure */
typedef struct {
    float temperature_c;        // Temperature in Celsius
    float humidity_percent;     // Relative humidity in %
    float pressure_hpa;         // Atmospheric pressure in hPa
    uint16_t voc_index;        // VOC Index (1-500)
    uint16_t nox_index;        // NOx Index (1-500)
    uint16_t voc_raw;          // VOC raw signal
    uint16_t nox_raw;          // NOx raw signal
    uint16_t co2_ppm;          // CO2 concentration in ppm
    bool sensor_error;         // Sensor error flag
    char error_text[64];       // Error description
} aeris_sensor_state_t;

/* I2C Bus Configuration - Dual Bus Setup
 * Bus 0 (GPIO14/15): Self-heating sensors - SCD4x + SGP41
 * Bus 1 (GPIO3/4): Environmental sensors - SHT4x + DPS368
 */
#define AERIS_I2C_BUS0_SDA_PIN  14    // GPIO14 - I2C Bus 0 SDA
#define AERIS_I2C_BUS0_SCL_PIN  15    // GPIO15 - I2C Bus 0 SCL
#define AERIS_I2C_BUS1_SDA_PIN  3     // GPIO3 - I2C Bus 1 SDA
#define AERIS_I2C_BUS1_SCL_PIN  4     // GPIO4 - I2C Bus 1 SCL
#define AERIS_I2C_FREQ_HZ       100000  // 100kHz I2C clock

/* I2C Bus 0 Sensors (GPIO6/7) */
#define SCD40_I2C_ADDR          0x62  // SCD4x CO2 Sensor - Fixed I2C address
#define SGP41_I2C_ADDR          0x59  // SGP41 VOC/NOx Sensor - Fixed I2C address

/* I2C Bus 1 Sensors (GPIO22/23) */
#define SHT4X_I2C_ADDR          0x44  // SHT4x Temperature/Humidity - 0x44, 0x45, or 0x46 depending on model
#define DPS368_I2C_ADDR         0x77  // DPS368 Pressure Sensor - 0x77 (SDO floating/high) or 0x76 (SDO low)

/**
 * @brief Initialize air quality sensor driver
 * 
 * @return ESP_OK on success
 */
esp_err_t aeris_driver_init(void);

/**
 * @brief Get current sensor readings
 * 
 * @param state Pointer to state structure to fill
 * @return ESP_OK on success
 */
esp_err_t aeris_get_sensor_data(aeris_sensor_state_t *state);

/**
 * @brief Read temperature and humidity
 * 
 * @param temp_c Pointer to temperature in Celsius
 * @param humidity Pointer to humidity in %
 * @return ESP_OK on success
 */
esp_err_t aeris_read_temp_humidity(float *temp_c, float *humidity);

/**
 * @brief Read atmospheric pressure
 * 
 * @param pressure_hpa Pointer to pressure in hPa
 * @return ESP_OK on success
 */
esp_err_t aeris_read_pressure(float *pressure_hpa);

/**
 * @brief Read VOC Index
 * 
 * @param voc_index Pointer to VOC Index value
 * @return ESP_OK on success
 */
esp_err_t aeris_read_voc(uint16_t *voc_index);

/**
 * @brief Read NOx Index
 * 
 * @param nox_index Pointer to NOx Index value
 * @return ESP_OK on success
 */
esp_err_t aeris_read_nox(uint16_t *nox_index);

/**
 * @brief Read VOC and NOx raw signals from SGP41
 * 
 * @param voc_raw Pointer to VOC raw signal
 * @param nox_raw Pointer to NOx raw signal
 * @return ESP_OK on success
 */
esp_err_t aeris_read_voc_nox_raw(uint16_t *voc_raw, uint16_t *nox_raw);

/**
 * @brief Read CO2 concentration
 * 
 * @param co2_ppm Pointer to CO2 in ppm
 * @return ESP_OK on success
 */
esp_err_t aeris_read_co2(uint16_t *co2_ppm);

/**
 * @brief Set temperature offset compensation for self-heating
 * 
 * The SHT45 sensor may read higher than actual ambient temperature due to
 * self-heating from nearby components (SCD40, SGP41, ESP32, etc.).
 * This offset is subtracted from the raw sensor reading.
 * 
 * @param offset_c Temperature offset in degrees Celsius (typically 2.0 to 4.0)
 *                 Positive value = sensor reads high, will be subtracted
 */
void aeris_set_temperature_offset(float offset_c);

/**
 * @brief Get current temperature offset compensation value
 * 
 * @return Temperature offset in degrees Celsius
 */
float aeris_get_temperature_offset(void);

/**
 * @brief Set humidity offset compensation
 * 
 * @param offset_percent Humidity offset in percent RH (typically 0 to 5)
 *                       Positive value = sensor reads high, will be subtracted
 */
void aeris_set_humidity_offset(float offset_percent);

/**
 * @brief Get current humidity offset compensation value
 * 
 * @return Humidity offset in percent RH
 */
float aeris_get_humidity_offset(void);

#ifdef __cplusplus
}
#endif

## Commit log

2025-11-03 Refactor Aeris Driver for Air Quality Sensors
    - Renamed and updated the Aeris driver files to reflect air quality sensor functionality instead of HVAC control.
    - Changed communication method from UART to I2C for sensor interaction.
    - Introduced new data structures and functions to handle temperature, humidity, pressure, PM, VOC Index, and CO2 readings.
    - Implemented initialization and reading functions for various air quality sensors.
    - Updated Zigbee integration to expose air quality sensor data as endpoints.
    - Removed obsolete HVAC-related code and definitions, focusing solely on air quality metrics.
2025-11-03 Add PMSA003A particulate matter sensor support with UART communication
2025-11-03 Add SGP41 VOC and NOx sensor support; update driver and README
2025-11-04 Add SCD40 CO2 sensor support; update driver and README
2025-11-04 Refactor Zigbee endpoint configuration and add OTA validation functions; implement all sensor endpoints with proper attribute updates
2025-11-04 Update README and source files to reflect Zigbee Router configuration changes
2025-11-05 feat: Enhance Zigbee Router with RGB LED Indicators for Air Quality
    - Updated README.md to include new features and detailed descriptions of RGB LED indicators.
    - Modified CMakeLists.txt to include RMT driver dependency for LED control.
    - Refactored aeris_driver.c to initialize RGB LED indicators and handle LED configuration via Zigbee.
    - Created led_indicator.c and led_indicator.h for managing RGB LED operations, including color settings based on air quality sensor readings.
    - Added support for configurable LED thresholds for CO2, VOC, PM2.5, and Humidity.
    - Implemented real-time visual feedback through 4 RGB LEDs, providing immediate status on air quality parameters.
2025-11-05 feat: Implement individual LED control via bitmask and update related configurations
2025-11-05 feat: Add PMSA003A power management and polling interval configuration
2025-11-05 feat: Add Zigbee status LED support with blinking indication during network join
2025-11-15 feat: Update README to include new Status LED endpoint and enhance PM thresholds; refactor µg/m³ to µg/m3 for consistency
2025-11-15 Refactor doc structure for improved readability and maintainability
2025-11-17 Add symbol library for ESP32-C6FH4-SuperMini to the project and update project GPIOs
2025-11-19 PCB version 1.0 Update PIN assignment for better PCB routing
2025-11-20 Final update for PCB version 1.0 before manufacturing
2025-11-20 Update .gitignore to remove unecessary PCB files
2025-11-20 Fix paths in .gitignore for PCB backups and cache files
2025-12-02 feat: Implement WiFi WebSocket logging for real-time console output
    - Added WiFi logging functionality to broadcast logs over WebSocket.
    - Introduced configuration options in board.h for enabling/disabling logging and setting WiFi credentials.
    - Created wifi_log.c and wifi_log.h for handling WiFi connections and WebSocket communication.
    - Updated led_indicator.c to use a shared RMT channel for LED control.
    - Modified esp_zb_aeris.c to initialize WiFi logging during app startup.
    - Adjusted aeris_driver.h for I2C address corrections and driver inclusions.
2025-12-02 fix: Update boot button and WiFi logging configurations for debugging
2025-12-03 feat: Add temperature and humidity offset compensation, and LED brightness control
2025-12-03 feat: Implement settings persistence for user-configurable parameters in NVS
2025-12-03 Refactor PCB design and update sensor configurations
    - Changed footprint references for LED components to use the correct library.
    - Enhanced README with detailed sensor conversion formulas and calibration notes.
    - Updated aeris_driver.c to enforce minimum sampling intervals for SGP41 and SCD40 sensors.
    - Disabled automatic self-calibration for SCD40 to maintain stable CO2 baseline.
    - Adjusted LPS22HB sensor configuration to use one-shot mode for power savings.
2025-12-08 feat: Update image builder tool path and enable brownout detection settings
2025-12-10 fix: Correct SHT45 measurement time and update brownout detection configuration
2025-12-10 fix: Update paths in CMakeLists (Linux)
2025-12-18 Remove Plantower sensor
2025-12-18 refactor: Update README and code to reflect removal of PM1.0, PM2.5, and PM10 sensors; adjust LED configurations accordingly
2025-12-19 Rename PCB files
2025-12-19 PCVB : Work in progress
2025-12-19 Summary of Changes: Hardware Configuration (board.h & aeris_driver.h): I2C Bus 0: GPIO14 (SDA) + GPIO15 (SCL) → SCD4x (CO2) + SGP41 (VOC/NOx) I2C Bus 1: GPIO3 (SDA) + GPIO4 (SCL) → SHT4x (Temp/Humidi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
2025-12-19 feat: Implement fan control driver for Aeris_Lite
    - Added fan_control.c and fan_control.h to manage PWM speed control and RPM monitoring for a 5V 4-wire PWM fan.
    - Integrated GPIO configuration for fan power control and tachometer pulse counting.
    - Implemented functions for initializing the fan system, setting power and speed, retrieving RPM, and checking fan status.
    - Added adaptive control based on temperature and air quality sensor readings.
    - Defined fan operating modes and status structure for better management and monitoring.

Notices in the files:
README.md:
License: GPL v3
License: CC BY-NC-SA 4.0
